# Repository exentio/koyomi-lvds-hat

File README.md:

# Project Koyomi - display testing hat

This is the first part of the development of Project Koyomi, read [this blog post](https://blog.exentio.sexy/2023/12/11/project-koyomi-planning.html)
for more.  
The purpose of this Raspberry Pi hat is to test and play around with the
display of the Vaio P before further development of the motherboard.  

The board is currently tested and working [as shown here](https://blog.exentio.sexy/2024/05/09/project-koyomi-update-3.html)!

The board uses Texas Instruments' SN75LVDS83B LVDS transmitter using the Pi's
DPI signals to send video out to the display. The final motherboard will use a
DVI receiver to free up the Raspberry's GPIO, a small converter board is in
development and [you can find it here](https://github.com/exentio/koyomi-hdmi-lvds).  

The display connector is made by I-PEX, and the model numbers are
`20374-030E-31`/`20374-R30E-31`, they're the same but the 0 variant seems to be
more common.  
The display, in my case a LT080EE04100 by Toshiba (it should be the same for
all Vaio Ps), has no backlight driver, and for that the backlight pins are
broken out, allowing testing of different drivers.  
The driver will be controlled using software I2C since all the hardware I2C
pins are already used by DPI. The assigned GPIOs are 23 for SDA and 24 for SCL.
More info about software I2C on [this page](https://learn.adafruit.com/raspberry-pi-i2c-clock-stretching-fixes/software-i2c).

The current settings used in `config.txt` (on top of the default) is:  
```
dtparam=i2c_arm=off
dtparam=spi=off
display_auto_detect=0
dtoverlay=vc4-kms-dpi-generic
dtparam=hactive=1600,hfp=32,hsync=65,hbp=97
dtparam=vactive=768,vfp=1,vsync=1,vbp=8
dtparam=width-mm=182,height-mm=87
dtparam=clock-frequency=83600000,rgb666
framebuffer_width=1600
framebuffer_height=768
dtoverlay=i2c-gpio,i2c_gpio_sda=23,i2c_gpio_scl=24
disable_overscan=1
```
---

### Forking guidelines
I hope that this design will inspire people to work on similar projects, and
that they'll be used as references to learn how to work on similar projects!  
If you want to make any contribution, you're welcome to fork and send a pull
request, as long as LLMs are not directly involved and you understand your
changes: please refer to (HUMAN.md)[https://github.com/exentio/koyomi-lvds-hat/blob/main/HUMAN.md], thank you.  

You're also welcome to make changes to any part of this project to implement
different design choices, without having to send a pull request; however, if
your fork takes a completely different direction from Koyomi and breaks
compatibility, I kindly ask you to drop the name "Koyomi" from your project.
Please also remove every art on the PCB, if possible (wouldn't make sense to
have my face on a completely different project anyway).  
This can't and won't be enforced, so I'm just asking informally to please
respect this request, if you want to use my designs.  

### Commercial use
I purposely decided to allow commercial use for this project for two reasons: I
would be happy if modernized Vaio Ps and Koyomi were to be used in professional
contexts, and to let people distribute PCBs so everyone can build their own,
without having to sell parts myself, which is not something I can handle.  

If you plan to sell boards and parts, I only have these simple requests:  
- Please make them reasonably affordable and don't mark them up absurdly, I
want this project to be approachable from every point of view.  
- If you're profiting from reselling my designs, please donate something back
to the people who made the designs you're selling.  
- Don't remove any drawings/art on the PCBs, but you're allowed to add your own.  

None of these can and will be enforced, so I'm just asking you to respect the
time and hard work the other contributors and I have poured into designing
Koyomi.

---

Huge thanks to Arya ([@CRImier](https://github.com/CRImier)) for her help during most phases of the design!

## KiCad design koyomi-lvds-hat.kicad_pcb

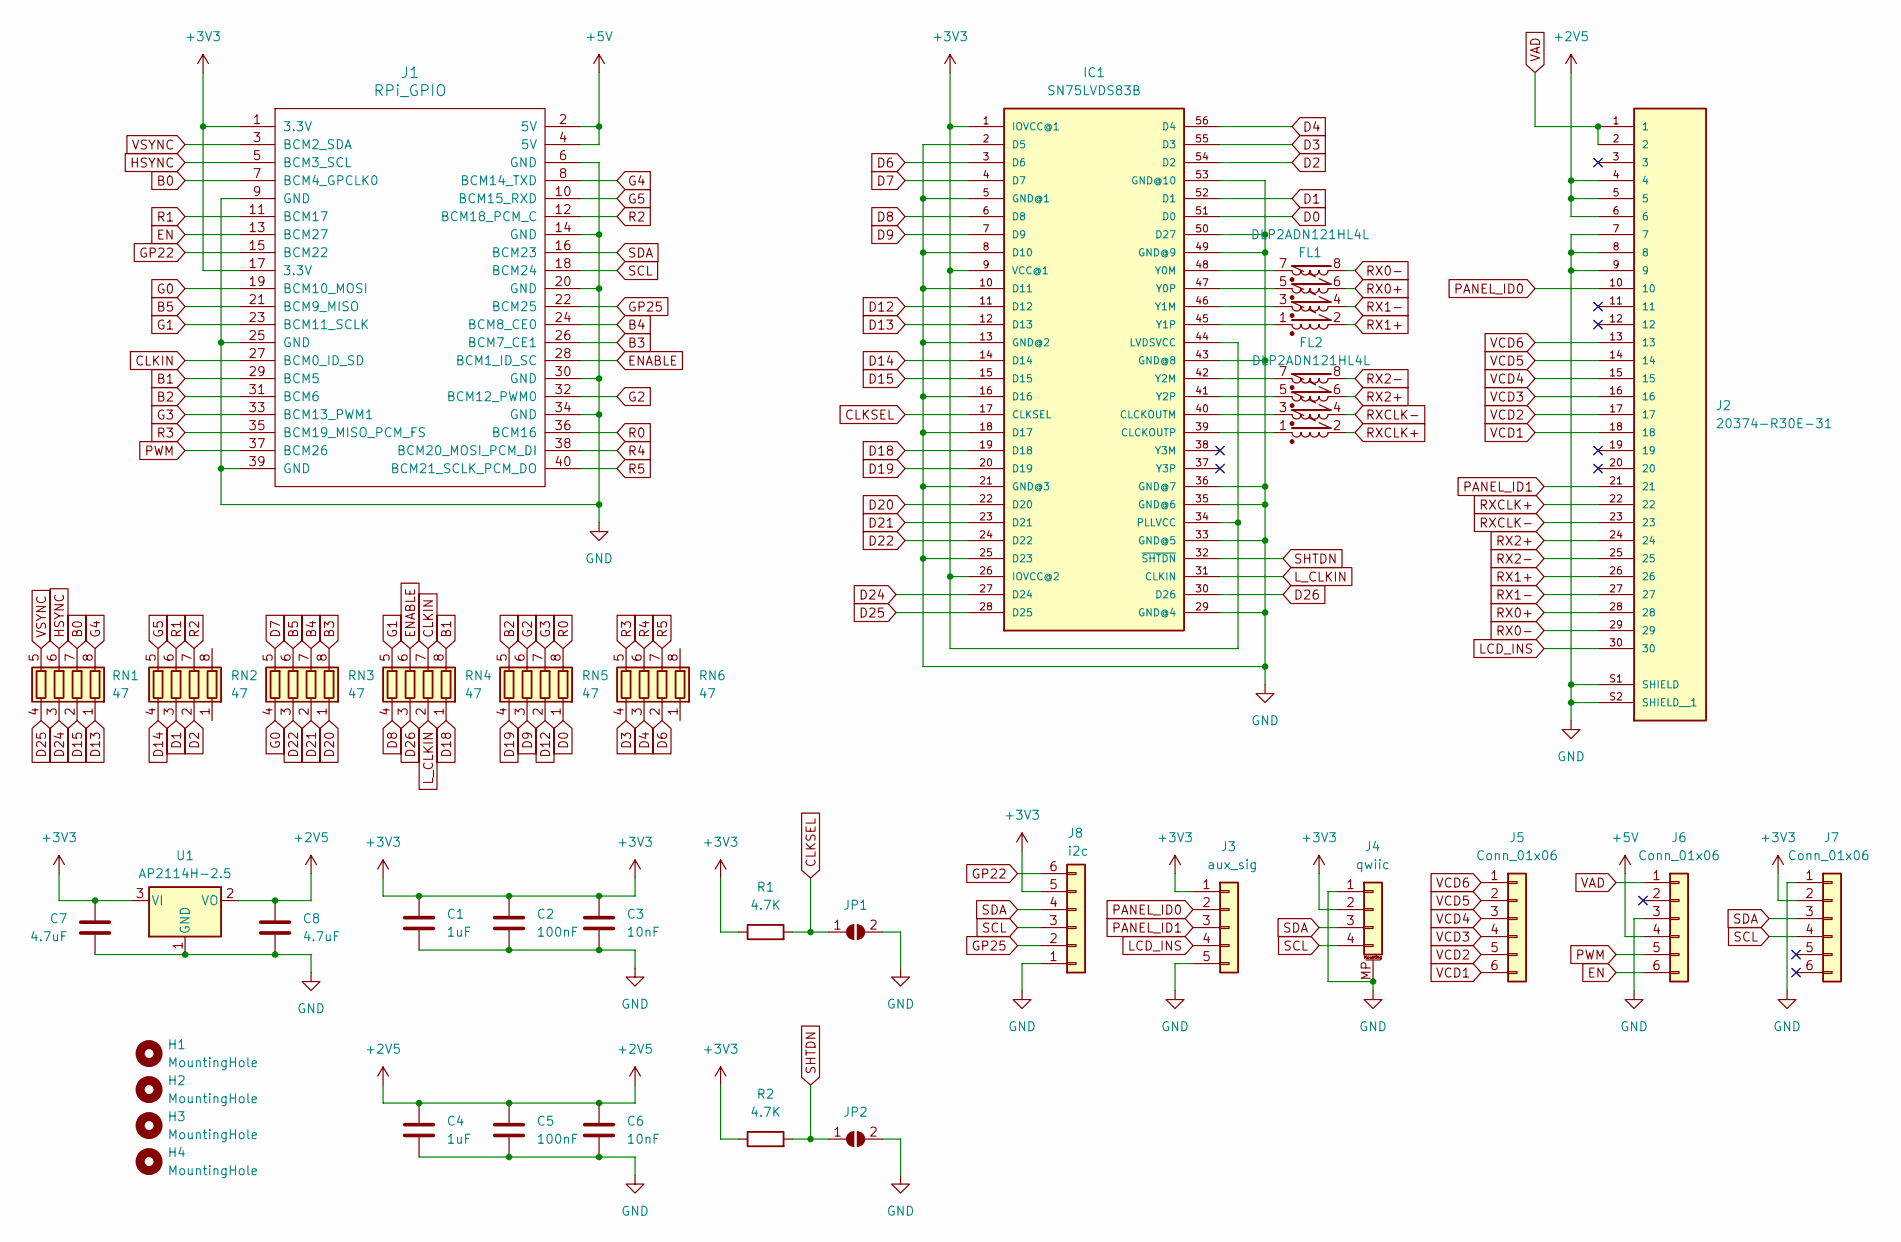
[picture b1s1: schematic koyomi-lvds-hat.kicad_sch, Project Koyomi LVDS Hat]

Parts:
C1, C4: 1uF; C_0603_1608Metric_Pad1.08x0.95mm_HandSolder
C2, C5: 100nF; C_0603_1608Metric_Pad1.08x0.95mm_HandSolder
C3, C6: 10nF; C_0603_1608Metric_Pad1.08x0.95mm_HandSolder
C7, C8: 4.7uF; C_0603_1608Metric_Pad1.08x0.95mm_HandSolder
FL1, FL2: DLP2ADN121HL4L; Murata_DLP2ADN121HL4L
H1, H2, H3, H4: MountingHole; RPi_Hat_Mounting_Hole
IC1: SN75LVDS83B; TSSOP56; DIGIKEY 296-24529-6-ND
J1: RPi_GPIO; Samtec_HLE-120-02-XXX-DV-BE-XX-XX
J2: 20374-R30E-31; I-PEX_20374-R30E-31; PARTREV 24
J3: aux_sig; PinSocket_1x05_P2.54mm_Vertical
J4: qwiic; JST_SH_SM04B-SRSS-TB_1x04-1MP_P1.00mm_Horizontal
J5, J6, J7: Conn_01x06; PinHeader_1x06_P2.54mm_Vertical
J8: i2c; PinHeader_1x06_P2.54mm_Vertical
JP1: CLKSEL; SolderJumper-2_P1.3mm_Open_RoundedPad1.0x1.5mm
JP2: SHTDN; SolderJumper-2_P1.3mm_Open_RoundedPad1.0x1.5mm
R1, R2: 4.7K; R_0603_1608Metric_Pad0.98x0.95mm_HandSolder
RN1, RN2, RN3, RN4, RN5, RN6: 47; R_Array_Convex_4x0603
U1: AP2114H-2.5; SOT-223-3_TabPin2

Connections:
+2V5: C4.1, C5.1, C6.1, C8.1, J2.4, J2.5, J2.6, U1.2 (VO)
+3V3: C1.1, C2.1, C3.1, C7.1, IC1.1 (IOVCC@1), IC1.9 (VCC@1), IC1.26 (IOVCC@2), IC1.34 (PLLVCC), IC1.44 (LVDSVCC), J1.1 (3.3V), J1.17 (3.3V), J3.1, J4.2, J7.2, J8.5, R1.1, R2.1, U1.3 (VI)
+5V: J1.2 (5V), J1.4 (5V), J6.4
B0: J1.7 (BCM4_GPCLK0), RN1.7 (R2.2)
B1: J1.29 (BCM5), RN4.8 (R1.2)
B2: J1.31 (BCM6), RN5.5 (R4.2)
B3: J1.26 (BCM7_CE1), RN3.8 (R1.2)
B4: J1.24 (BCM8_CE0), RN3.7 (R2.2)
B5: J1.21 (BCM9_MISO), RN3.6 (R3.2)
CLKIN: J1.27 (BCM0_ID_SD), RN4.7 (R2.2)
CLKSEL: IC1.17 (CLKSEL), JP1.1 (A), R1.2
D0: IC1.51 (D0), RN5.1 (R1.1)
D1: IC1.52 (D1), RN2.3 (R3.1)
D2: IC1.54 (D2), RN2.2 (R2.1)
D3: IC1.55 (D3), RN6.4 (R4.1)
D4: IC1.56 (D4), RN6.3 (R3.1)
D6: IC1.3 (D6), RN6.2 (R2.1)
D7: IC1.4 (D7), RN3.5 (R4.2)
D8: IC1.6 (D8), RN4.4 (R4.1)
D9: IC1.7 (D9), RN5.3 (R3.1)
D12: IC1.11 (D12), RN5.2 (R2.1)
D13: IC1.12 (D13), RN1.1 (R1.1)
D14: IC1.14 (D14), RN2.4 (R4.1)
D15: IC1.15 (D15), RN1.2 (R2.1)
D18: IC1.19 (D18), RN4.1 (R1.1)
D19: IC1.20 (D19), RN5.4 (R4.1)
D20: IC1.22 (D20), RN3.1 (R1.1)
D21: IC1.23 (D21), RN3.2 (R2.1)
D22: IC1.24 (D22), RN3.3 (R3.1)
D24: IC1.27 (D24), RN1.3 (R3.1)
D25: IC1.28 (D25), RN1.4 (R4.1)
D26: IC1.30 (D26), RN4.3 (R3.1)
EN: J1.13 (BCM27), J6.6
ENABLE: J1.28 (BCM1_ID_SC), RN4.6 (R3.2)
G0: J1.19 (BCM10_MOSI), RN3.4 (R4.1)
G1: J1.23 (BCM11_SCLK), RN4.5 (R4.2)
G2: J1.32 (BCM12_PWM0), RN5.6 (R3.2)
G3: J1.33 (BCM13_PWM1), RN5.7 (R2.2)
G4: J1.8 (BCM14_TXD), RN1.8 (R1.2)
G5: J1.10 (BCM15_RXD), RN2.5 (R4.2)
GND: C1.2, C2.2, C3.2, C4.2, C5.2, C6.2, C7.2, C8.2, IC1.2 (D5), IC1.5 (GND@1), IC1.8 (D10), IC1.10 (D11), IC1.13 (GND@2), IC1.16 (D16), IC1.18 (D17), IC1.21 (GND@3), IC1.25 (D23), IC1.29 (GND@4), IC1.33 (GND@5), IC1.35 (GND@6), IC1.36 (GND@7), IC1.43 (GND@8), IC1.49 (GND@9), IC1.50 (D27), IC1.53 (GND@10), J1.6 (GND), J1.9 (GND), J1.14 (GND), J1.20 (GND), J1.25 (GND), J1.30 (GND), J1.34 (GND), J1.39 (GND), J2.7, J2.8, J2.9, J2.S1 (SHIELD), J2.S2 (SHIELD__1), J3.5, J4.1, J4.MP (MountPin), J6.3, J7.1, J8.1, JP1.2 (B), JP2.2 (B), U1.1 (GND)
GP22: J1.15 (BCM22), J8.6
GP25: J1.22 (BCM25), J8.2
HSYNC: J1.5 (BCM3_SCL), RN1.6 (R3.2)
LCD_INS: J2.30, J3.4
L_CLKIN: IC1.31 (CLKIN), RN4.2 (R2.1)
unnamed: FL2.3, IC1.40 (CLCKOUTM)
unnamed: FL2.1, IC1.39 (CLCKOUTP)
unnamed: FL1.7, IC1.48 (Y0M)
unnamed: FL1.5, IC1.47 (Y0P)
unnamed: FL1.3, IC1.46 (Y1M)
unnamed: FL1.1, IC1.45 (Y1P)
unnamed: FL2.7, IC1.42 (Y2M)
unnamed: FL2.5, IC1.41 (Y2P)
PANEL_ID0: J2.10, J3.2
PANEL_ID1: J2.21, J3.3
PWM: J1.37 (BCM26), J6.5
R0: J1.36 (BCM16), RN5.8 (R1.2)
R1: J1.11 (BCM17), RN2.6 (R3.2)
R2: J1.12 (BCM18_PCM_C), RN2.7 (R2.2)
R3: J1.35 (BCM19_MISO_PCM_FS), RN6.5 (R4.2)
R4: J1.38 (BCM20_MOSI_PCM_DI), RN6.6 (R3.2)
R5: J1.40 (BCM21_SCLK_PCM_DO), RN6.7 (R2.2)
RX0+: FL1.6, J2.28
RX0-: FL1.8, J2.29
RX1+: FL1.2, J2.26
RX1-: FL1.4, J2.27
RX2+: FL2.6, J2.24
RX2-: FL2.8, J2.25
RXCLK+: FL2.2, J2.22
RXCLK-: FL2.4, J2.23
SCL: J1.18 (BCM24), J4.4, J7.4, J8.3
SDA: J1.16 (BCM23), J4.3, J7.3, J8.4
SHTDN: IC1.32 (~SHTDN), JP2.1 (A), R2.2
VAD: J2.1, J2.2, J6.1
VCD1: J2.18, J5.6
VCD2: J2.17, J5.5
VCD3: J2.16, J5.4
VCD4: J2.15, J5.3
VCD5: J2.14, J5.2
VCD6: J2.13, J5.1
VSYNC: J1.3 (BCM2_SDA), RN1.5 (R4.2)

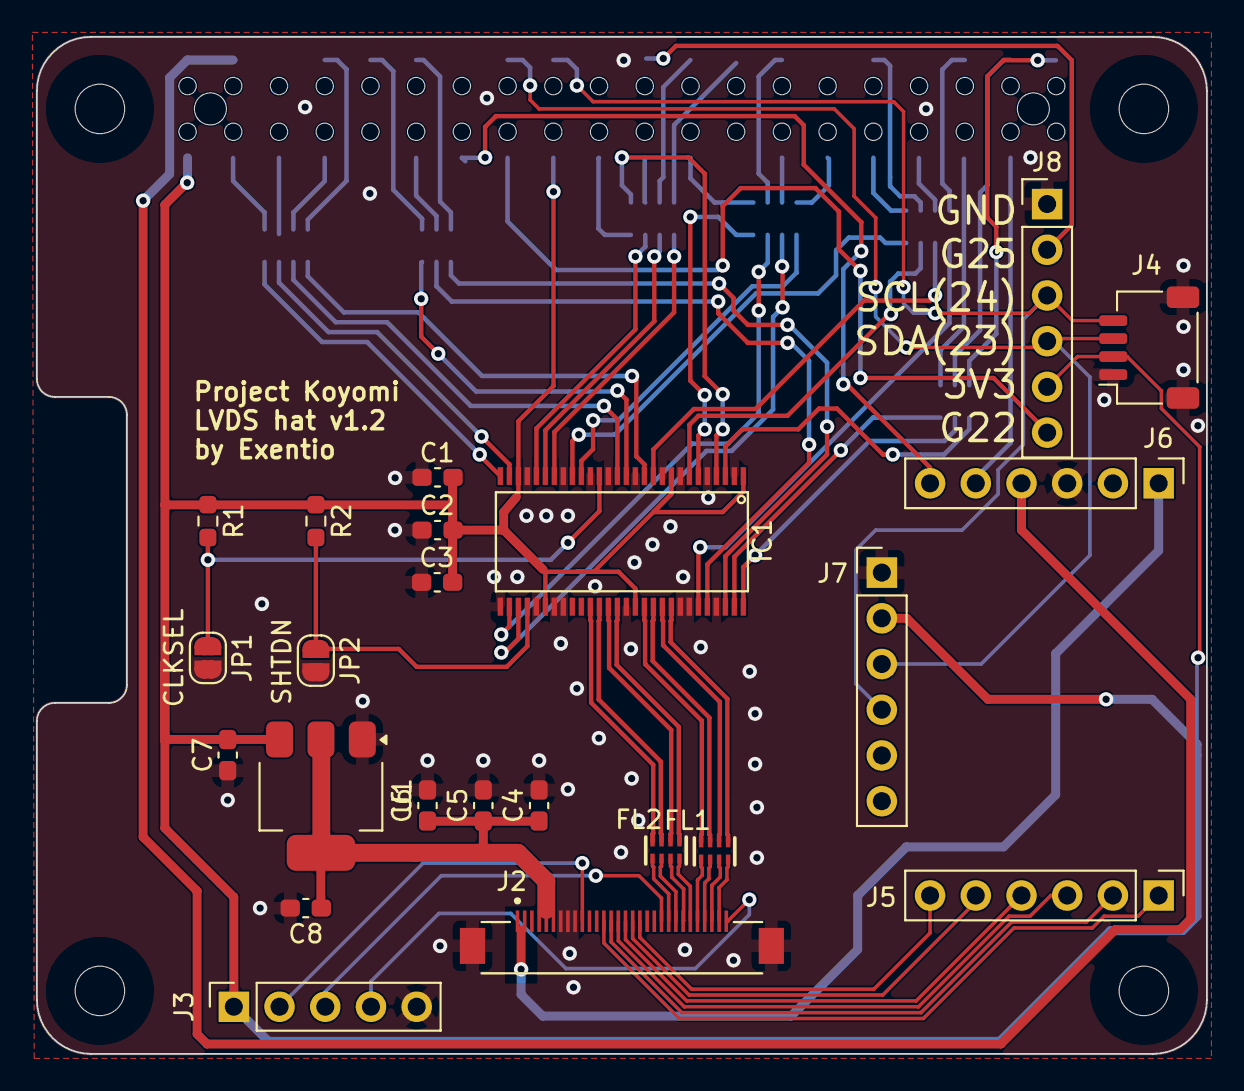
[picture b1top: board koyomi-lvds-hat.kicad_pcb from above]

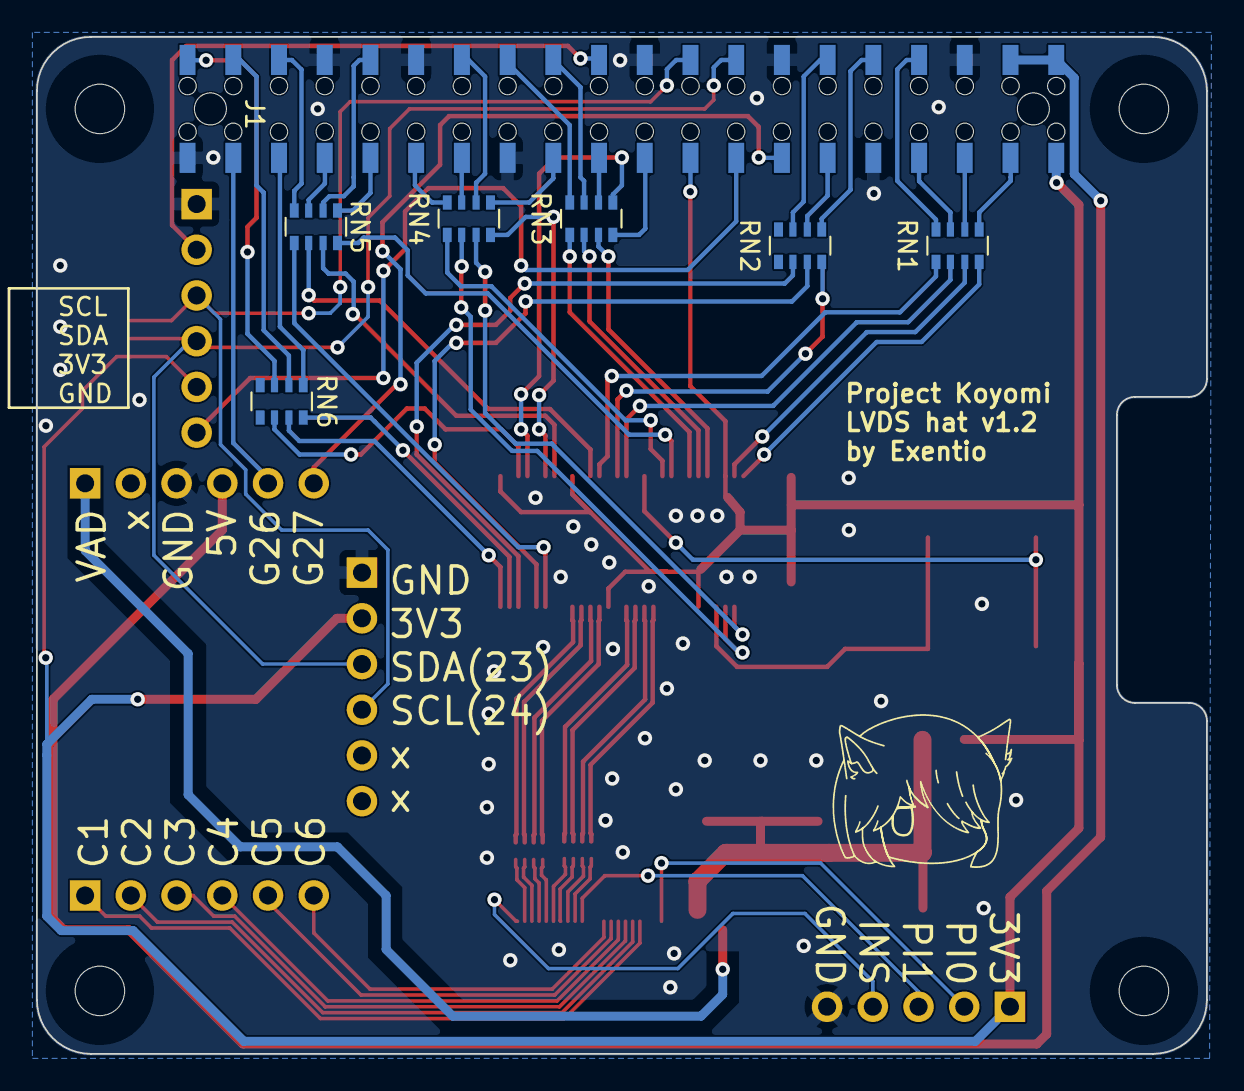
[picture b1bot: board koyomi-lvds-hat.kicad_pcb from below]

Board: 2 copper layers, 65.0 x 56.5 mm, 34 parts (7 on the bottom side), 82 nets.

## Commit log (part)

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2024-01-25 Minor fixes
2024-01-26 Restored previous LVDS traces
2024-03-18 RPi/breakout garden standard header with IO22 as INT and IO25 added on top; RGB tracks moved around a bit but length-matched anew
2024-03-18 Added silkscreen markings for all the headers
2024-03-30 Minor updates, added libraries
2024-03-30 Added 3D models, labels fix
2024-04-10 Added footprint for backlight driver pins
2024-04-25 Readme update
2024-04-26 v1.1 - fixed hat connector side, added series resistors
2024-04-26 Added LVDS common mode filters
2024-05-15 Add license
2024-07-21 Gerbers and JLCPCB files update
2024-08-01 Changed PCB art to simple silkscreen lines
2024-08-03 Update gerbers to reflect recent changes
2024-12-27 Fix GPIO footprint
2024-12-27 Fix JLCPCB rotations
2024-12-28 Readme change
